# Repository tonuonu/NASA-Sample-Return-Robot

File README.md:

NASA-Sample-Return-Robot
========================

Some code related to https://www.facebook.com/TeamKuukulgur

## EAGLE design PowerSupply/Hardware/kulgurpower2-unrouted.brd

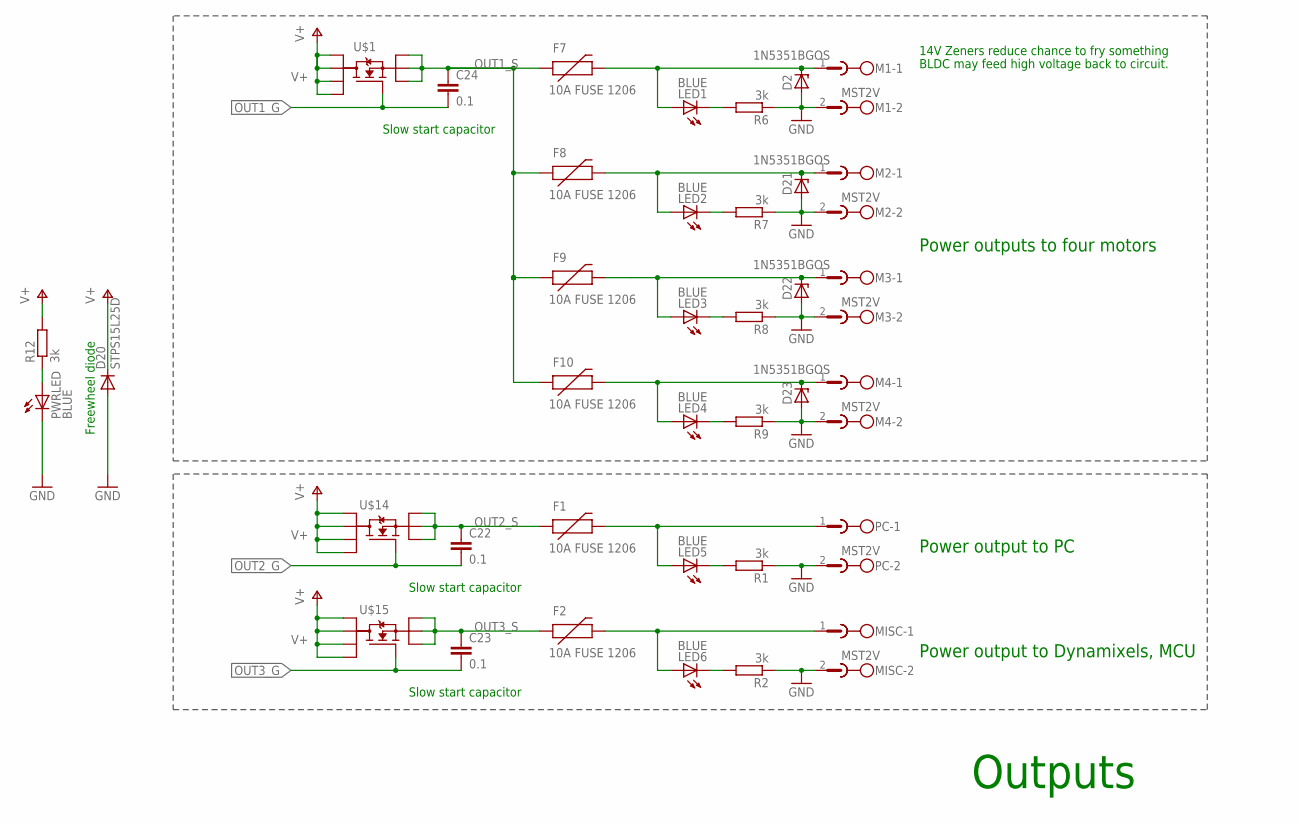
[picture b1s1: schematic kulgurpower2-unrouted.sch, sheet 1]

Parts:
C22, C23, C24: 0.1; C0603
D2, D21, D22, D23: 1N5351BGOS; C1702-15
D20: STPS15L25D; C221B1A
F1, F2, F7, F8, F9, F10: 10A FUSE 1206; PTC-1206
LED1, LED2, LED3, LED4, LED5, LED6: BLUE; CHIP-LED0603
M1, M2, M3, M4: MST2V; MSTBV2
MISC: MST2V; MSTBV2
PC: MST2V; MSTBV2
PWRLED: BLUE; CHIP-LED0603
R1, R2, R6, R7, R8, R9, R12: 3k; R0603
U$1, U$14, U$15: AON6500; POWER56

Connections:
GND: D2.A, D20.A, D21.A, D22.A, D23.A, M1.2, M2.2, M3.2, M4.2, MISC.2, PC.2, PWRLED.C, R1.1, R2.1, R6.1, R7.1, R8.1, R9.1; also elsewhere on the board
unnamed: LED1.C, R6.2
unnamed: LED2.C, R7.2
unnamed: LED3.C, R8.2
unnamed: LED4.C, R9.2
unnamed: LED5.C, R1.2
unnamed: LED6.C, R2.2
unnamed: PWRLED.A, R12.1
OUT1_G: C24.2, U$1.P$4 (G); also elsewhere on the board
OUT1_S: C24.1, F7.1, F8.1, F9.1, F10.1, U$1.P$1 (S1), U$1.P$2 (S2), U$1.P$3 (S3); also elsewhere on the board
OUT2_G: C22.2, U$14.P$4 (G); also elsewhere on the board
OUT2_S: C22.1, F1.1, U$14.P$1 (S1), U$14.P$2 (S2), U$14.P$3 (S3); also elsewhere on the board
OUT3_G: C23.2, U$15.P$4 (G); also elsewhere on the board
OUT3_S: C23.1, F2.1, U$15.P$1 (S1), U$15.P$2 (S2), U$15.P$3 (S3); also elsewhere on the board
PWR1: D2.C, F7.2, LED1.A, M1.1
PWR2: D21.C, F8.2, LED2.A, M2.1
PWR3: D22.C, F9.2, LED3.A, M3.1
PWR4: D23.C, F10.2, LED4.A, M4.1
PWR5: F1.2, LED5.A, PC.1
PWR6: F2.2, LED6.A, MISC.1
V+: D20.C, R12.2, U$1.P$5 (D4), U$1.P$6 (D3), U$1.P$7 (D2), U$1.P$8 (D1), U$14.P$5 (D4), U$14.P$6 (D3), U$14.P$7 (D2), U$14.P$8 (D1), U$15.P$5 (D4), U$15.P$6 (D3), U$15.P$7 (D2), U$15.P$8 (D1); also elsewhere on the board

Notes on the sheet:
Freewheel diode
BLDC may feed high voltage back to circuit.
14V Zeners reduce chance to fry something
Outputs
Power outputs to four motors
Power output to PC
Power output to Dynamixels, MCU
Slow start capacitor

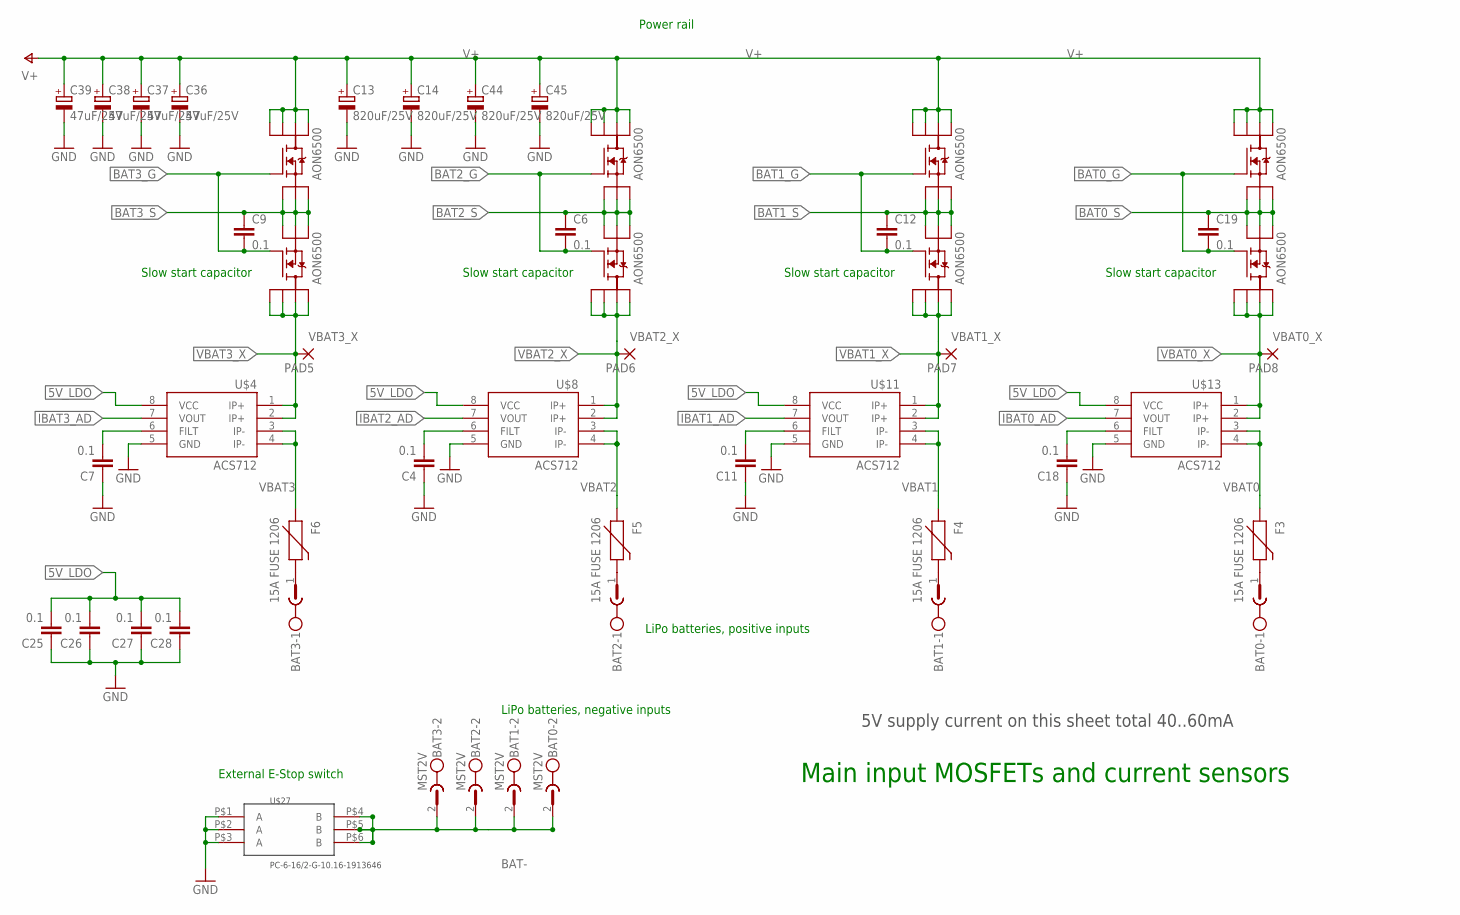
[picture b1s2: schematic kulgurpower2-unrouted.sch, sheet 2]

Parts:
BAT0, BAT1, BAT2, BAT3: MST2V; MSTBV2
C4, C6, C7, C9, C11, C12, C18, C19, C25, C26, C27, C28: 0.1; C0603
C13, C14, C44, C45: 820uF/25V; 153CLV-1014
C36, C37: 47uF/25V; C/6032-28R
C38, C39: 47uF/25V; 175TMP-0810
F3, F4, F5, F6: 15A FUSE 1206; PTC-1206
PAD5, PAD6, PAD7, PAD8: 1,6/0,9
U$2, U$3, U$5, U$6, U$7, U$9, U$10, U$12: AON6500; POWER56
U$4, U$8, U$11, U$13: ACS712; SO08
U$27: PC-6-16/2-G-10.16-1913646; PC-6-16/2-G-10.16

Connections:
5V_LDO: C25.2, C26.2, C27.2, C28.2, U$4.8 (VCC), U$8.8 (VCC), U$11.8 (VCC), U$13.8 (VCC); also elsewhere on the board
BAT0_G: C19.2, U$5.P$4 (G), U$12.P$4 (G); also elsewhere on the board
BAT0_S: C19.1, U$5.P$1 (S1), U$5.P$2 (S2), U$5.P$3 (S3), U$12.P$1 (S1), U$12.P$2 (S2), U$12.P$3 (S3); also elsewhere on the board
BAT1_G: C12.2, U$9.P$4 (G), U$10.P$4 (G); also elsewhere on the board
BAT1_S: C12.1, U$9.P$1 (S1), U$9.P$2 (S2), U$9.P$3 (S3), U$10.P$1 (S1), U$10.P$2 (S2), U$10.P$3 (S3); also elsewhere on the board
BAT2_G: C6.2, U$6.P$4 (G), U$7.P$4 (G); also elsewhere on the board
BAT2_S: C6.1, U$6.P$1 (S1), U$6.P$2 (S2), U$6.P$3 (S3), U$7.P$1 (S1), U$7.P$2 (S2), U$7.P$3 (S3); also elsewhere on the board
BAT3_G: C9.2, U$2.P$4 (G), U$3.P$4 (G); also elsewhere on the board
BAT3_S: C9.1, U$2.P$1 (S1), U$2.P$2 (S2), U$2.P$3 (S3), U$3.P$1 (S1), U$3.P$2 (S2), U$3.P$3 (S3); also elsewhere on the board
BAT-: BAT0.2, BAT1.2, BAT2.2, BAT3.2, U$27.P$4 (B), U$27.P$5 (B), U$27.P$6 (B)
GND: C4.1, C7.1, C11.1, C13.-, C14.-, C18.1, C25.1, C26.1, C27.1, C28.1, C36.-, C37.-, C38.-, C39.-, C44.-, C45.-, U$4.5 (GND), U$8.5 (GND), U$11.5 (GND), U$13.5 (GND), U$27.P$1 (A), U$27.P$2 (A), U$27.P$3 (A); also elsewhere on the board
IBAT0_AD: U$13.7 (VOUT); also elsewhere on the board
IBAT1_AD: U$11.7 (VOUT); also elsewhere on the board
IBAT2_AD: U$8.7 (VOUT); also elsewhere on the board
IBAT3_AD: U$4.7 (VOUT); also elsewhere on the board
unnamed: BAT0.1, F3.2
unnamed: BAT3.1, F6.2
unnamed: BAT1.1, F4.2
unnamed: C4.2, U$8.6 (FILT)
unnamed: BAT2.1, F5.2
unnamed: C11.2, U$11.6 (FILT)
unnamed: C7.2, U$4.6 (FILT)
unnamed: C18.2, U$13.6 (FILT)
V+: C13.+, C14.+, C36.+, C37.+, C38.+, C39.+, C44.+, C45.+, U$2.P$5 (D4), U$2.P$6 (D3), U$2.P$7 (D2), U$2.P$8 (D1), U$5.P$5 (D4), U$5.P$6 (D3), U$5.P$7 (D2), U$5.P$8 (D1), U$6.P$5 (D4), U$6.P$6 (D3), U$6.P$7 (D2), U$6.P$8 (D1), U$9.P$5 (D4), U$9.P$6 (D3), U$9.P$7 (D2), U$9.P$8 (D1); also elsewhere on the board
VBAT0: F3.1, U$13.3 (IP-), U$13.4 (IP-)
VBAT0_X: PAD8.1, U$12.P$5 (D4), U$12.P$6 (D3), U$12.P$7 (D2), U$12.P$8 (D1), U$13.1 (IP+), U$13.2 (IP+); also elsewhere on the board
VBAT1: F4.1, U$11.3 (IP-), U$11.4 (IP-)
VBAT1_X: PAD7.1, U$10.P$5 (D4), U$10.P$6 (D3), U$10.P$7 (D2), U$10.P$8 (D1), U$11.1 (IP+), U$11.2 (IP+); also elsewhere on the board
VBAT2: F5.1, U$8.3 (IP-), U$8.4 (IP-)
VBAT2_X: PAD6.1, U$7.P$5 (D4), U$7.P$6 (D3), U$7.P$7 (D2), U$7.P$8 (D1), U$8.1 (IP+), U$8.2 (IP+); also elsewhere on the board
VBAT3: F6.1, U$4.3 (IP-), U$4.4 (IP-)
VBAT3_X: PAD5.1, U$3.P$5 (D4), U$3.P$6 (D3), U$3.P$7 (D2), U$3.P$8 (D1), U$4.1 (IP+), U$4.2 (IP+); also elsewhere on the board

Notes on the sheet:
External E-Stop switch
LiPo batteries, positive inputs
LiPo batteries, negative inputs
Power rail
Main input MOSFETs and current sensors
5V supply current on this sheet total 40..60mA
Slow start capacitor

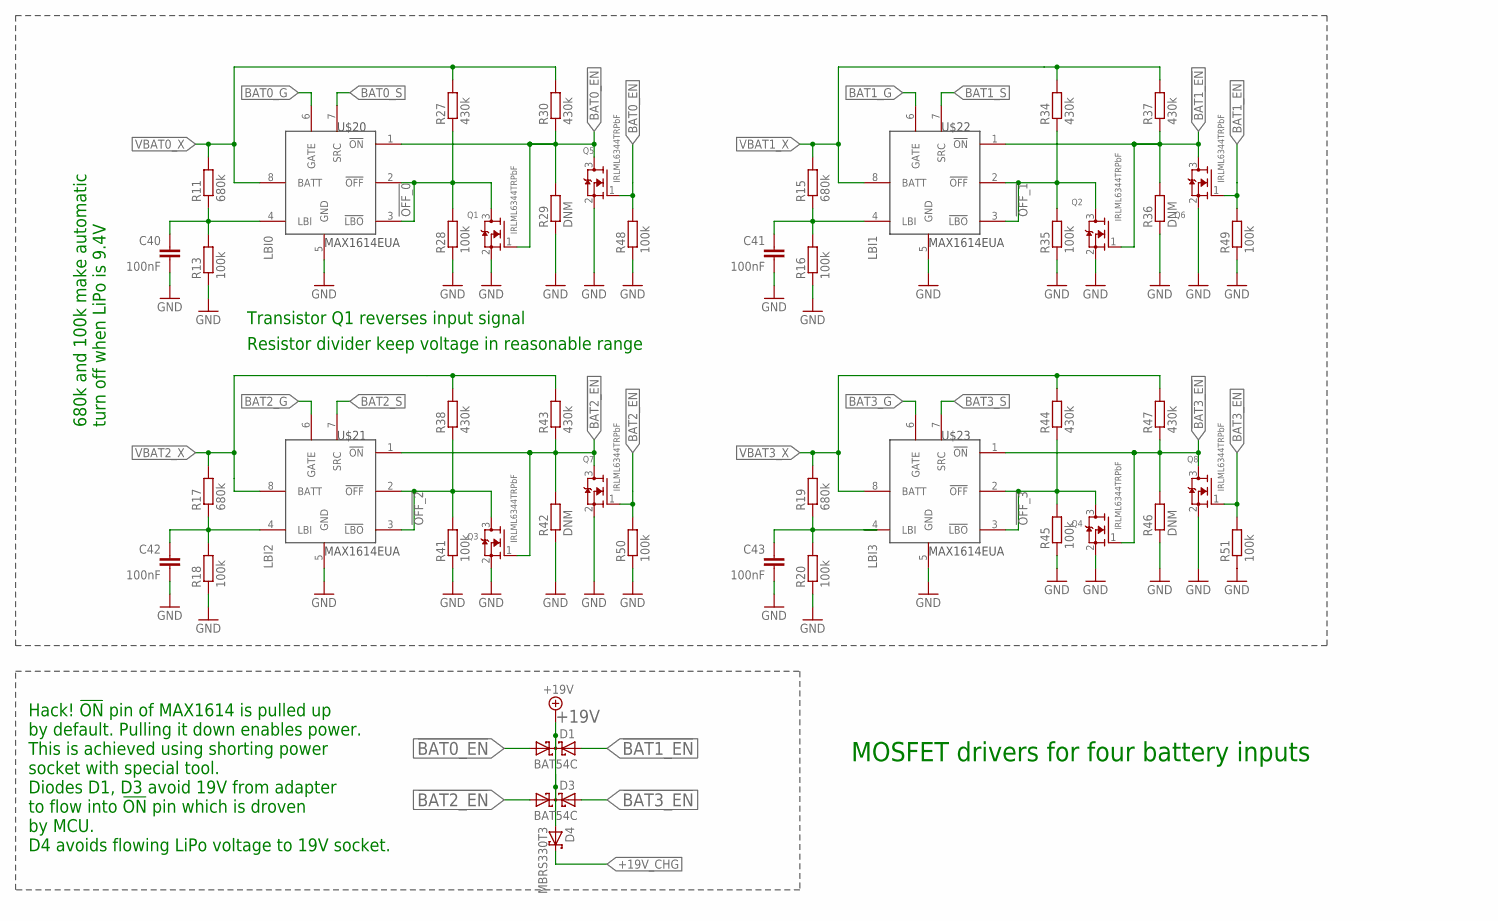
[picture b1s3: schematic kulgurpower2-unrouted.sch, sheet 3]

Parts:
C40, C41, C42, C43: 100nF; C0603
D1, D3: BAT54C; SOT23
D4: MBRS330T3; SMC
Q1, Q2, Q3, Q4, Q5, Q6, Q7, Q8: IRLML6344TRPbF; SOT23
R11, R15, R17, R19: 680k; R0603
R13, R16, R18, R20, R28, R35, R41, R45, R48, R49, R50, R51: 100k; R0603
R27, R30, R34, R37, R38, R43, R44, R47: 430k; R0603
R29, R36, R42, R46: DNM; R0603
U$20, U$21, U$22, U$23: MAX1614EUA

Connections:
!BAT0_EN: D1.1 (A1), Q1.1 (G), Q5.3 (D), R29.2, R30.1, U$20.1 (!ON)
!BAT1_EN: D1.2 (A2), Q2.1 (G), Q6.3 (D), R36.2, R37.1, U$22.1 (!ON)
!BAT2_EN: D3.1 (A1), Q3.1 (G), Q7.3 (D), R42.2, R43.1, U$21.1 (!ON)
!BAT3_EN: D3.2 (A2), Q4.1 (G), Q8.3 (D), R46.2, R47.1, U$23.1 (!ON)
!OFF_0: Q1.3 (D), R27.1, R28.2, U$20.2 (!OFF), U$20.3 (!LBO)
!OFF_1: Q2.3 (D), R34.1, R35.2, U$22.2 (!OFF), U$22.3 (!LBO)
!OFF_2: Q3.3 (D), R38.1, R41.2, U$21.2 (!OFF), U$21.3 (!LBO)
!OFF_3: Q4.3 (D), R44.1, R45.2, U$23.2 (!OFF), U$23.3 (!LBO)
+19V: D1.3 (CC), D3.3 (CC), D4.A; also elsewhere on the board
+19V_CHG: D4.C; also elsewhere on the board
BAT0_EN: Q5.1 (G), R48.2; also elsewhere on the board
BAT0_G: U$20.6 (GATE); also elsewhere on the board
BAT0_S: U$20.7 (SRC); also elsewhere on the board
BAT1_EN: Q6.1 (G), R49.2; also elsewhere on the board
BAT1_G: U$22.6 (GATE); also elsewhere on the board
BAT1_S: U$22.7 (SRC); also elsewhere on the board
BAT2_EN: Q7.1 (G), R50.2; also elsewhere on the board
BAT2_G: U$21.6 (GATE); also elsewhere on the board
BAT2_S: U$21.7 (SRC); also elsewhere on the board
BAT3_EN: Q8.1 (G), R51.2; also elsewhere on the board
BAT3_G: U$23.6 (GATE); also elsewhere on the board
BAT3_S: U$23.7 (SRC); also elsewhere on the board
GND: C40.2, C41.2, C42.2, C43.2, Q1.2 (S), Q2.2 (S), Q3.2 (S), Q4.2 (S), Q5.2 (S), Q6.2 (S), Q7.2 (S), Q8.2 (S), R13.1, R16.1, R18.1, R20.1, R28.1, R29.1, R35.1, R36.1, R41.1, R42.1, R45.1, R46.1, R48.1, R49.1, R50.1, R51.1, U$20.5 (GND), U$21.5 (GND), U$22.5 (GND), U$23.5 (GND); also elsewhere on the board
LBI0: C40.1, R11.1, R13.2, U$20.4 (LBI)
LBI1: C41.1, R15.1, R16.2, U$22.4 (LBI)
LBI2: C42.1, R17.1, R18.2, U$21.4 (LBI)
LBI3: C43.1, R19.1, R20.2, U$23.4 (LBI)
VBAT0_X: R11.2, R27.2, R30.2, U$20.8 (BATT); also elsewhere on the board
VBAT1_X: R15.2, R34.2, R37.2, U$22.8 (BATT); also elsewhere on the board
VBAT2_X: R17.2, R38.2, R43.2, U$21.8 (BATT); also elsewhere on the board
VBAT3_X: R19.2, R44.2, R47.2, U$23.8 (BATT); also elsewhere on the board

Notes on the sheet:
680k and 100k make automatic turn off when LiPo is 9.4V
MOSFET drivers for four battery inputs
Hack! !ON! pin of MAX1614 is pulled up by default. Pulling it down enables power. This is achieved using shorting power socket with special tool. Diodes D1, D3 avoid 19V from adapter to flow into !ON! pin which is droven by MCU. D4 avoids flowing LiPo voltage to 19V socket.
Resistor divider keep voltage in reasonable range
Transistor Q1 reverses input signal

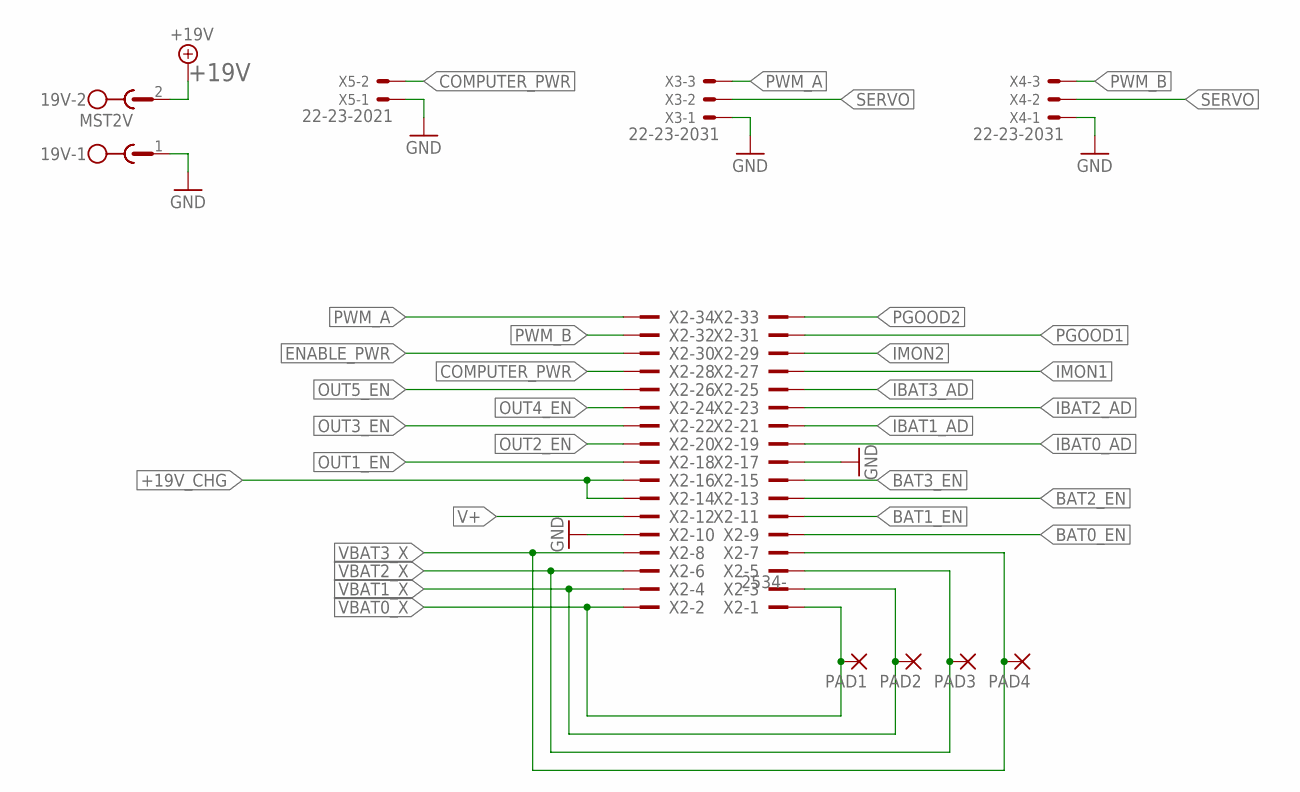
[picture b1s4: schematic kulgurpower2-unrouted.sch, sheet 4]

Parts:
19V: MST2V; MSTBV2
PAD1, PAD2, PAD3, PAD4: 1,6/0,9
X2: 2534-; PAK100/2500-34
X3, X4: 22-23-2031
X5: 22-23-2021

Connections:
+19V: 19V.2; also elsewhere on the board
+19V_CHG: X2.14, X2.16; also elsewhere on the board
BAT0_EN: X2.9; also elsewhere on the board
BAT1_EN: X2.11; also elsewhere on the board
BAT2_EN: X2.13; also elsewhere on the board
BAT3_EN: X2.15; also elsewhere on the board
COMPUTER_PWR: X2.28, X5.2
ENABLE_PWR: X2.30; also elsewhere on the board
GND: 19V.1, X2.10, X2.17, X3.1, X4.1, X5.1; also elsewhere on the board
IBAT0_AD: X2.19; also elsewhere on the board
IBAT1_AD: X2.21; also elsewhere on the board
IBAT2_AD: X2.23; also elsewhere on the board
IBAT3_AD: X2.25; also elsewhere on the board
IMON1: X2.27; also elsewhere on the board
IMON2: X2.29; also elsewhere on the board
OUT1_EN: X2.18; also elsewhere on the board
OUT2_EN: X2.20; also elsewhere on the board
OUT3_EN: X2.22; also elsewhere on the board
OUT4_EN: X2.24; also elsewhere on the board
OUT5_EN: X2.26; also elsewhere on the board
PGOOD1: X2.31; also elsewhere on the board
PGOOD2: X2.33; also elsewhere on the board
PWM_A: X2.34, X3.3
PWM_B: X2.32, X4.3
SERVO: X3.2, X4.2; also elsewhere on the board
V+: X2.12; also elsewhere on the board
VBAT0_X: PAD1.1, X2.1, X2.2; also elsewhere on the board
VBAT1_X: PAD2.1, X2.3, X2.4; also elsewhere on the board
VBAT2_X: PAD3.1, X2.5, X2.6; also elsewhere on the board
VBAT3_X: PAD4.1, X2.7, X2.8; also elsewhere on the board

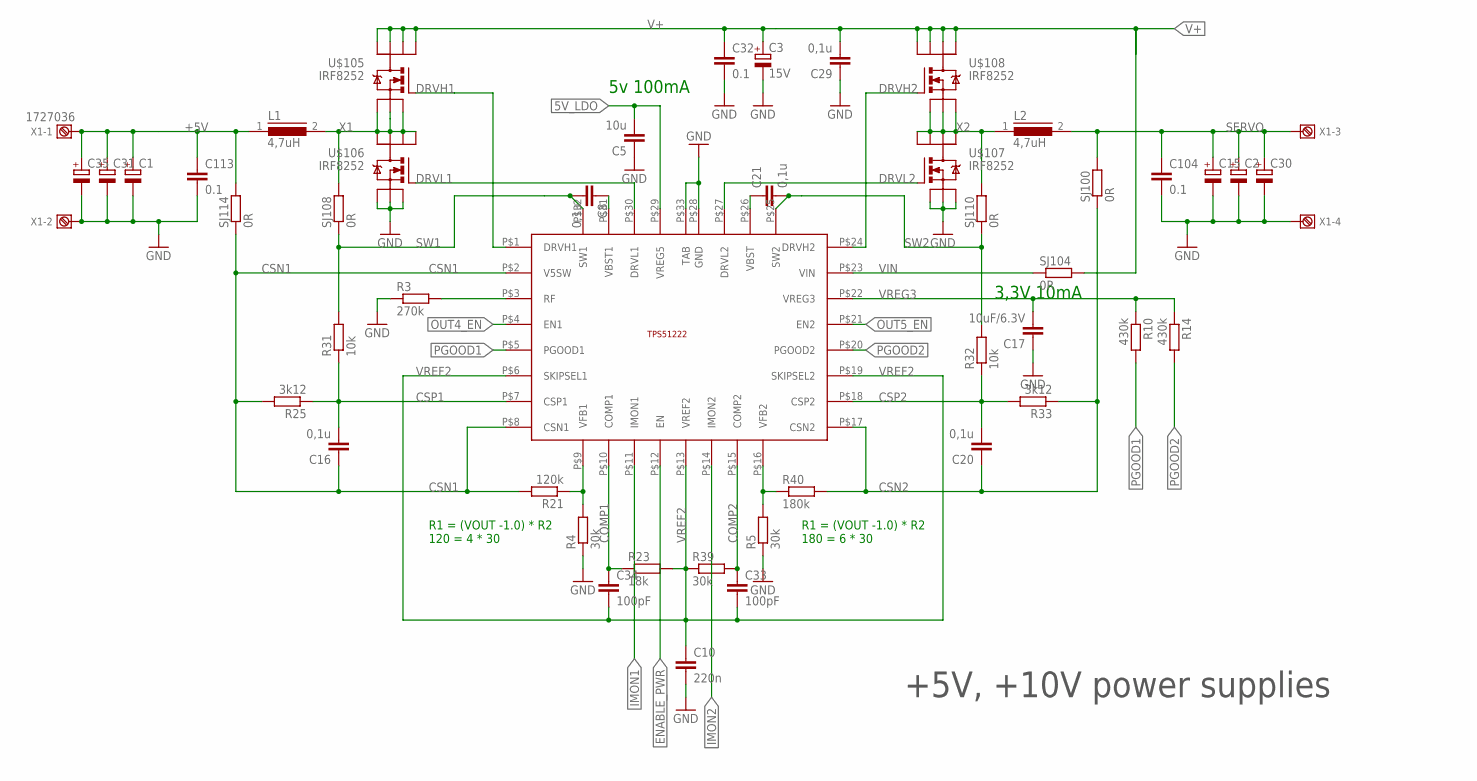
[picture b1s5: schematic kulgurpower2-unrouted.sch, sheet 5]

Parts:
C1, C2, C15, C30, C31, C35: CPOL-EUC/6032-28R; C/6032-28R
C3: 15V; C/6032-28R
C5: 10u; C1210
C8, C16, C20, C21, C29: 0,1u; C0603
C10: 220n; C0603
C17: 10uF/6.3V; C1210
C32, C104, C113: 0.1; C0603
C33, C34: 100pF; 0805
L1, L2: 4,7uH; DR125
R3: 270k; R0603
R4, R5, R39: 30k; R0603
R10, R14: 430k; R0603
R21: 120k; R0603
R23: 18k; R0603
R25, R33: 3k12; R0603
R31, R32: 10k; R0603
R40: 180k; R0603
SJ100, SJ104, SJ108, SJ110, SJ114: 0R; R0603
U$17: TPS51222RTVT; QFN-32
U$105, U$106, U$107, U$108: IRF8252; SO8
X1: 1727036

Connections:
5V_LDO: C5.2, U$17.P$29 (VREG5); also elsewhere on the board
+5V: C1.+, C31.+, C35.+, C113.1, L1.1, SJ114.2, X1.1
COMP1: C34.1, R23.1, U$17.P$10 (COMP1)
COMP2: C33.1, R39.2, U$17.P$15 (COMP2)
CSN1: C16.1, R21.2, R25.2, SJ114.1, U$17.P$2 (V5SW), U$17.P$8 (CSN1)
CSN2: C20.1, R33.1, R40.2, SJ100.1, U$17.P$17 (CSN2)
CSP1: C16.2, R25.1, R31.1, U$17.P$7 (CSP1)
CSP2: C20.2, R32.1, R33.2, U$17.P$18 (CSP2)
DRVH1: U$17.P$1 (DRVH1), U$105.4 (G)
DRVH2: U$17.P$24 (DRVH2), U$108.4 (G)
DRVL1: U$17.P$30 (DRVL1), U$106.4 (G)
DRVL2: U$17.P$27 (DRVL2), U$107.4 (G)
ENABLE_PWR: U$17.P$12 (EN); also elsewhere on the board
GND: C1.-, C2.-, C3.-, C5.1, C10.2, C15.-, C17.1, C29.1, C30.-, C31.-, C32.2, C35.-, C104.2, C113.2, R3.1, R4.1, R5.1, U$17.P$28 (GND), U$17.P$33 (TAB), U$106.1 (S), U$106.2 (S), U$106.3 (S), U$107.1 (S), U$107.2 (S), U$107.3 (S), X1.2, X1.4; also elsewhere on the board
IMON1: U$17.P$11 (IMON1); also elsewhere on the board
IMON2: U$17.P$14 (IMON2); also elsewhere on the board
unnamed: R4.2, R21.1, U$17.P$9 (VFB1)
unnamed: R5.2, R40.1, U$17.P$16 (VFB2)
unnamed: R3.2, U$17.P$3 (RF)
unnamed: C8.1, U$17.P$31 (VBST1)
unnamed: C21.1, U$17.P$26 (VBST)
OUT4_EN: U$17.P$4 (EN1); also elsewhere on the board
OUT5_EN: U$17.P$21 (EN2); also elsewhere on the board
PGOOD1: R10.2, U$17.P$5 (PGOOD1); also elsewhere on the board
PGOOD2: R14.2, U$17.P$20 (PGOOD2); also elsewhere on the board
SERVO: C2.+, C15.+, C30.+, C104.1, L2.2, SJ100.2, X1.3; also elsewhere on the board
SW1: C8.2, R31.2, SJ108.1, U$17.P$32 (SW1)
SW2: C21.2, R32.2, SJ110.1, U$17.P$25 (SW2)
V+: C3.+, C29.2, C32.1, SJ104.2, U$105.5 (D), U$105.6 (D), U$105.7 (D), U$105.8 (D), U$108.5 (D), U$108.6 (D), U$108.7 (D), U$108.8 (D); also elsewhere on the board
VIN: SJ104.1, U$17.P$23 (VIN)
VREF2: C10.1, C33.2, C34.2, R23.2, R39.1, U$17.P$6 (SKIPSEL1), U$17.P$13 (VREF2), U$17.P$19 (SKIPSEL2)
VREG3: C17.2, R10.1, R14.1, U$17.P$22 (VREG3)
X1: L1.2, SJ108.2, U$105.1 (S), U$105.2 (S), U$105.3 (S), U$106.5 (D), U$106.6 (D), U$106.7 (D), U$106.8 (D)
X2: L2.1, SJ110.2, U$107.5 (D), U$107.6 (D), U$107.7 (D), U$107.8 (D), U$108.1 (S), U$108.2 (S), U$108.3 (S)

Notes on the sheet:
+5V, +10V power supplies
3,3V 10mA
5v 100mA
R1 = (VOUT -1.0) * R2 120 = 4 * 30
R1 = (VOUT -1.0) * R2 180 = 6 * 30

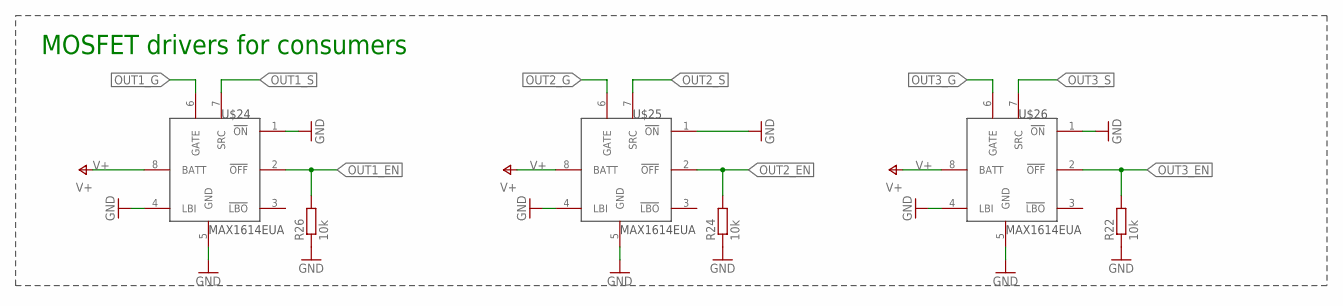
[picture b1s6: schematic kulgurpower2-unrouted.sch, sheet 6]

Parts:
R22, R24, R26: 10k; R0603
U$24, U$25, U$26: MAX1614EUA

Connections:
GND: R22.1, R24.1, R26.1, U$24.1 (!ON), U$24.4 (LBI), U$24.5 (GND), U$25.1 (!ON), U$25.4 (LBI), U$25.5 (GND), U$26.1 (!ON), U$26.4 (LBI), U$26.5 (GND); also elsewhere on the board
OUT1_EN: R26.2, U$24.2 (!OFF); also elsewhere on the board
OUT1_G: U$24.6 (GATE); also elsewhere on the board
OUT1_S: U$24.7 (SRC); also elsewhere on the board
OUT2_EN: R24.2, U$25.2 (!OFF); also elsewhere on the board
OUT2_G: U$25.6 (GATE); also elsewhere on the board
OUT2_S: U$25.7 (SRC); also elsewhere on the board
OUT3_EN: R22.2, U$26.2 (!OFF); also elsewhere on the board
OUT3_G: U$26.6 (GATE); also elsewhere on the board
OUT3_S: U$26.7 (SRC); also elsewhere on the board
V+: U$24.8 (BATT), U$25.8 (BATT), U$26.8 (BATT); also elsewhere on the board

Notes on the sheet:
MOSFET drivers for consumers

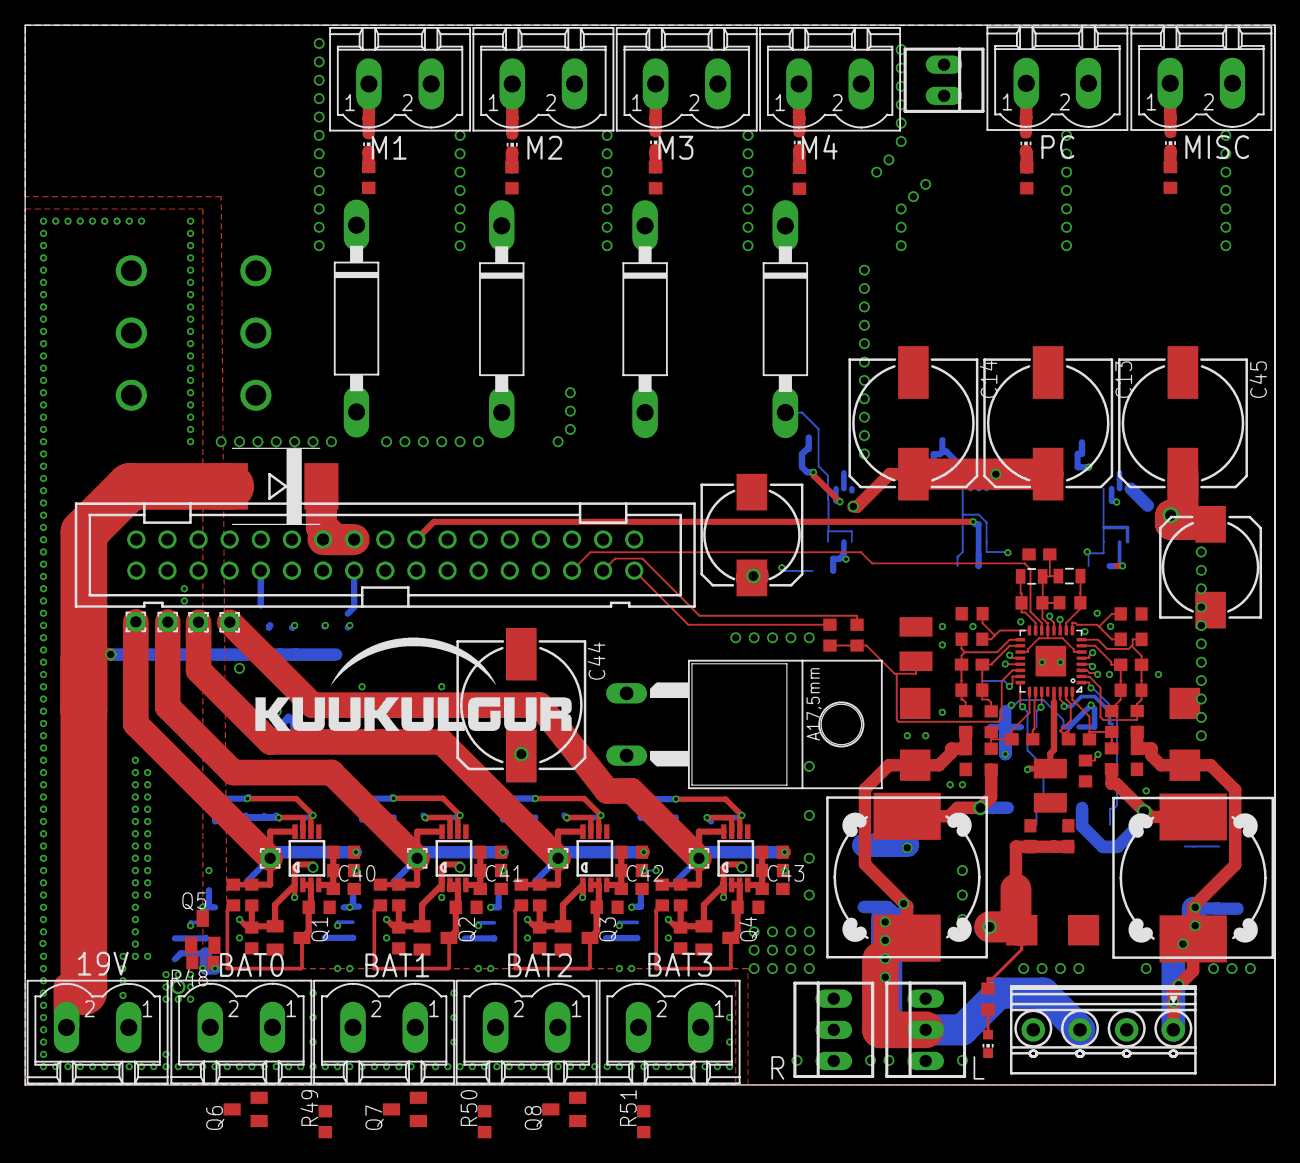
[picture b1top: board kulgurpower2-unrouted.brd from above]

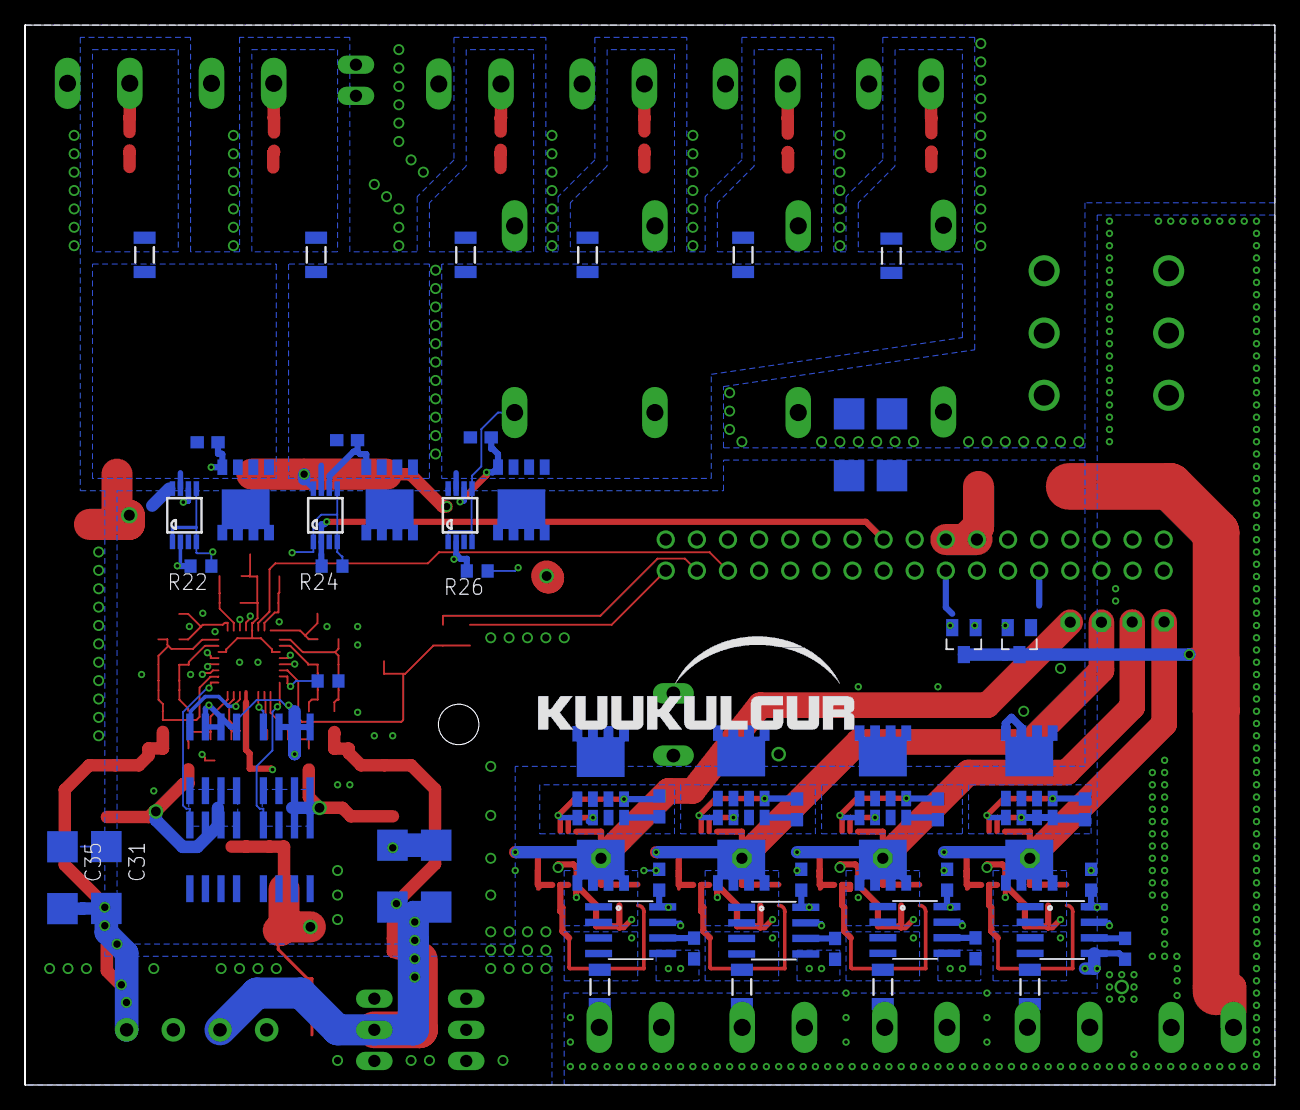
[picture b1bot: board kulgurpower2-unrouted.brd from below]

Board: 4 copper layers, 102.0 x 86.5 mm, 190 parts (59 on the bottom side), 106 nets.

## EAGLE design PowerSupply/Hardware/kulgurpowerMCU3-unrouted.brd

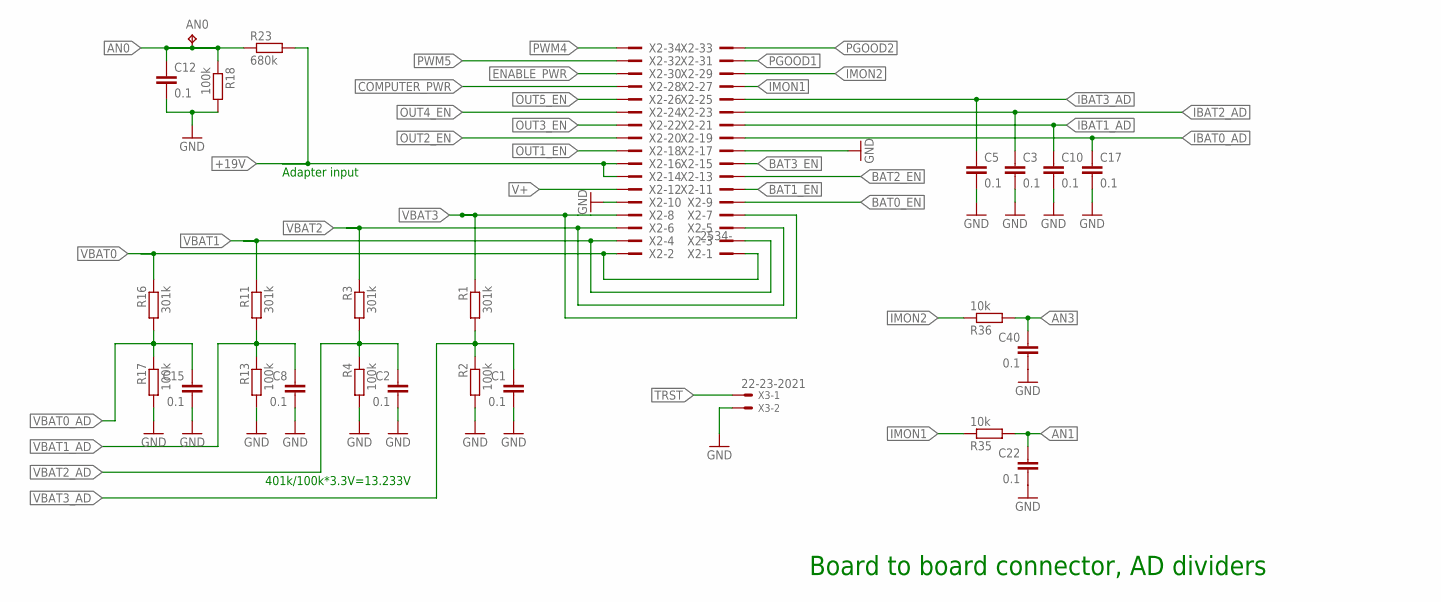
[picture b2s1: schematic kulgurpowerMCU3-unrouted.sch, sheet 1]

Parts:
AN0: TPB1,27; B1,27
C1, C2, C3, C5, C8, C10, C15, C17, C22, C40: 0.1; C0603
C12: 0.1; 0603-CAP
R1, R3, R11, R16: 301k; R0603
R2, R4, R13, R17, R18: 100k; R0603
R23: 680k; R0603
R35, R36: 10k; R0603
X2: 2534-; PAK100/2500-34
X3: 22-23-2021

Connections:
!TRST: X3.1; also elsewhere on the board
+19V: R23.2, X2.14, X2.16; also elsewhere on the board
AN0: AN0.TP, C12.1, R18.1, R23.1; also elsewhere on the board
AN1: C22.1, R35.2; also elsewhere on the board
AN3: C40.1, R36.2; also elsewhere on the board
BAT0_EN: X2.9; also elsewhere on the board
BAT1_EN: X2.11; also elsewhere on the board
BAT2_EN: X2.13; also elsewhere on the board
BAT3_EN: X2.15; also elsewhere on the board
COMPUTER_PWR: X2.28; also elsewhere on the board
ENABLE_PWR: X2.30; also elsewhere on the board
GND: C1.2, C2.2, C3.2, C5.2, C8.2, C10.2, C12.2, C15.2, C17.2, C22.2, C40.2, R2.2, R4.2, R13.2, R17.2, R18.2, X2.10, X2.17, X3.2; also elsewhere on the board
IBAT0_AD: C17.1, X2.19; also elsewhere on the board
IBAT1_AD: C10.1, X2.21; also elsewhere on the board
IBAT2_AD: C3.1, X2.23; also elsewhere on the board
IBAT3_AD: C5.1, X2.25; also elsewhere on the board
IMON1: R35.1, X2.27
IMON2: R36.1, X2.29
OUT1_EN: X2.18; also elsewhere on the board
OUT2_EN: X2.20; also elsewhere on the board
OUT3_EN: X2.22; also elsewhere on the board
OUT4_EN: X2.24; also elsewhere on the board
OUT5_EN: X2.26; also elsewhere on the board
PGOOD1: X2.31; also elsewhere on the board
PGOOD2: X2.33; also elsewhere on the board
PWM4: X2.34; also elsewhere on the board
PWM5: X2.32; also elsewhere on the board
V+: X2.12; also elsewhere on the board
VBAT0: R16.1, X2.1, X2.2; also elsewhere on the board
VBAT0_AD: C15.1, R16.2, R17.1; also elsewhere on the board
VBAT1: R11.1, X2.3, X2.4; also elsewhere on the board
VBAT1_AD: C8.1, R11.2, R13.1; also elsewhere on the board
VBAT2: R3.1, X2.5, X2.6; also elsewhere on the board
VBAT2_AD: C2.1, R3.2, R4.1; also elsewhere on the board
VBAT3: R1.1, X2.7, X2.8; also elsewhere on the board
VBAT3_AD: C1.1, R1.2, R2.1; also elsewhere on the board

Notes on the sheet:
401k/100k*3.3V=13.233V
Board to board connector, AD dividers
Adapter input

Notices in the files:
PowerSupply/Code/oled.cpp:
Copyright (c) 2013, 2014 Tonu Samuel
All rights reserved.
parts and their libraries:
SparkFun-PowerIC: Licensing: CC v3.0 Share-Alike You are welcome to use this library for commercial purposes.
